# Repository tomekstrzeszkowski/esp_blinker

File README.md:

# Motivation

In recent years, there has been a significant rise in the usage of digital devices across all age brackets, whether for work or leisure. Various therapeutic and management approaches have been suggested to address this issue, encompassing optical, medical, and ergonomic interventions.

One common recommendation from clinicians is to take regular breaks to reduce digital eye strain. This advice often includes following the 20-20-20 rule, which suggests taking breaks to focus on an object at least 20 feet (6 meters) away for at least 20 seconds every 20 minutes.

This project serves as a reminder to perform these exercises by toggling your external device on and off, ideally accompanied by a light indicator.

# Hardware 

## Electrical components and flashing

Full details are available in pcb folder
 - ESP8266 (ESP-12F)
 - Relay
 - SMD resistors
 - Button switches
 - Power supply

[PCB & Flashing](pcb/README.md)
 
# MQTT

## Home assistant

In devices & services add integration and search for MQTT. Add default integration.
In Apps, install app `Mosquitto broker`. Then go to config and add entry to logins.
Add new entry under MQTT and configure device, use `esp32/gpio/set` and switch component.

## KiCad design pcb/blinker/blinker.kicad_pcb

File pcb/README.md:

# PIN out

## 4 Socket PINs (J1)

1 - GND
2 - 3V3
3 - GPIO 3 / RXD
4 - GPIO 1 / TXD

## 2 Socket PINs

1, 2 GPIO0 - Boot up PINS (J2), connect for entering flashing mode

# Wiring ConnectionsUSB-to-UART 

 - USB TX - Connect to GPIO3 (RXD) on the ESP 
 - USB RX - Connect to GPIO1 (TXD) on the ESP
 - GND - Connect adapter GND to ESP GND

Enter into flashing mode
 - GPIO0 - Connect to GND, just connect 1 with 2 togeter via jumper

# Flashing
 - Connect UART to USB converter to J1, don't connect to USB yet
 - Enter flashing mode, connect 2 PINs together using jumper in J2 socket
 - Connect converter to USB, The blue LED should flicker once
 - Follow your preferred flashing IDE

## VS Code and PlatformIO

 - On the bottom bar, select esp12e, ttyUSB0
 - Click PlatformIO upload

At this point you should see percentage progress and LED should flash in some intervals

## esptool and PlatformIO

 - Install requirements.txt, this should install esptool and PlatformIO
 - PlatformIO builds firmware in this location
```
blinker/.pio/build/esp12e/firmware.bin
```
 - Build `firmware.bin` (list available targets `pio run --list-targets`)

```
pio run -e esp12e
```
This should produce firmware in the location as above.

 - Flash
```
esptool --port /dev/ttyUSB0 write-flash 0x00000 blinker/.pio/build/esp12e/firmware.bin
```

For ESP32

```
esptool --port /dev/ttyUSB0 --chip esp32 write-flash 0x10000 firmware.bin
```

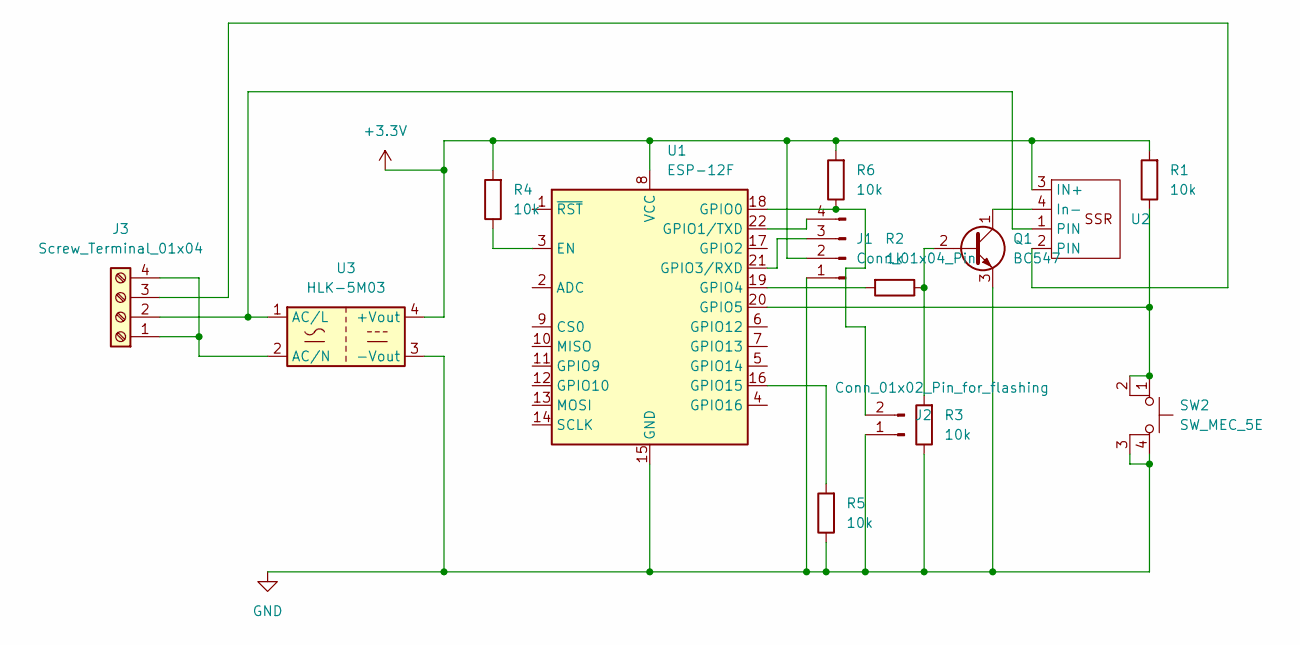
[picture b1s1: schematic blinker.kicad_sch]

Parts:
J1: Conn_01x04_Pin; PinHeader_1x04_P2.00mm_Vertical
J2: Conn_01x02_Pin_for_flashing; PinHeader_1x02_P2.00mm_Vertical
J3: Screw_Terminal_01x04; TerminalBlock_MaiXu_MX126-5.0-04P_1x04_P5.00mm
Q1: BC547; TO-92_Inline
R1, R3, R4, R5, R6: 10k; R_0805_2012Metric_Pad1.20x1.40mm_HandSolder
R2: 1k; R_0805_2012Metric_Pad1.20x1.40mm_HandSolder
SW2: SW_MEC_5E; SW_MEC_5GSH9
U1: ESP-12F; ESP-12E
U2: SSR-D3803HK
U3: HLK-5M03; Converter_ACDC_Hi-Link_HLK-5Mxx

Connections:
+3.3V: J1.2, R1.2, R4.2, R6.2, U1.8 (VCC), U2.3 (IN+), U3.4 (+Vout)
GND: J1.1, J2.1, Q1.3 (E), R3.1, R5.1, SW2.3 (K), SW2.4 (A), U1.15 (GND), U3.3 (-Vout)
unnamed: J1.3, U1.21 (GPIO3/RXD)
unnamed: J1.4, U1.22 (GPIO1/TXD)
unnamed: J2.2, R6.1, U1.18 (GPIO0)
unnamed: J3.1, J3.4, U3.2 (AC/N)
unnamed: J3.2, U2.1 (PIN), U3.1 (AC/L)
unnamed: J3.3, U2.2 (PIN)
unnamed: Q1.2 (B), R2.1, R3.2
unnamed: Q1.1 (C), U2.4 (In-)
unnamed: R4.1, U1.3 (EN)
unnamed: R2.2, U1.19 (GPIO4)
unnamed: R1.1, SW2.1, SW2.2, U1.20 (GPIO5)
unnamed: R5.2, U1.16 (GPIO15)

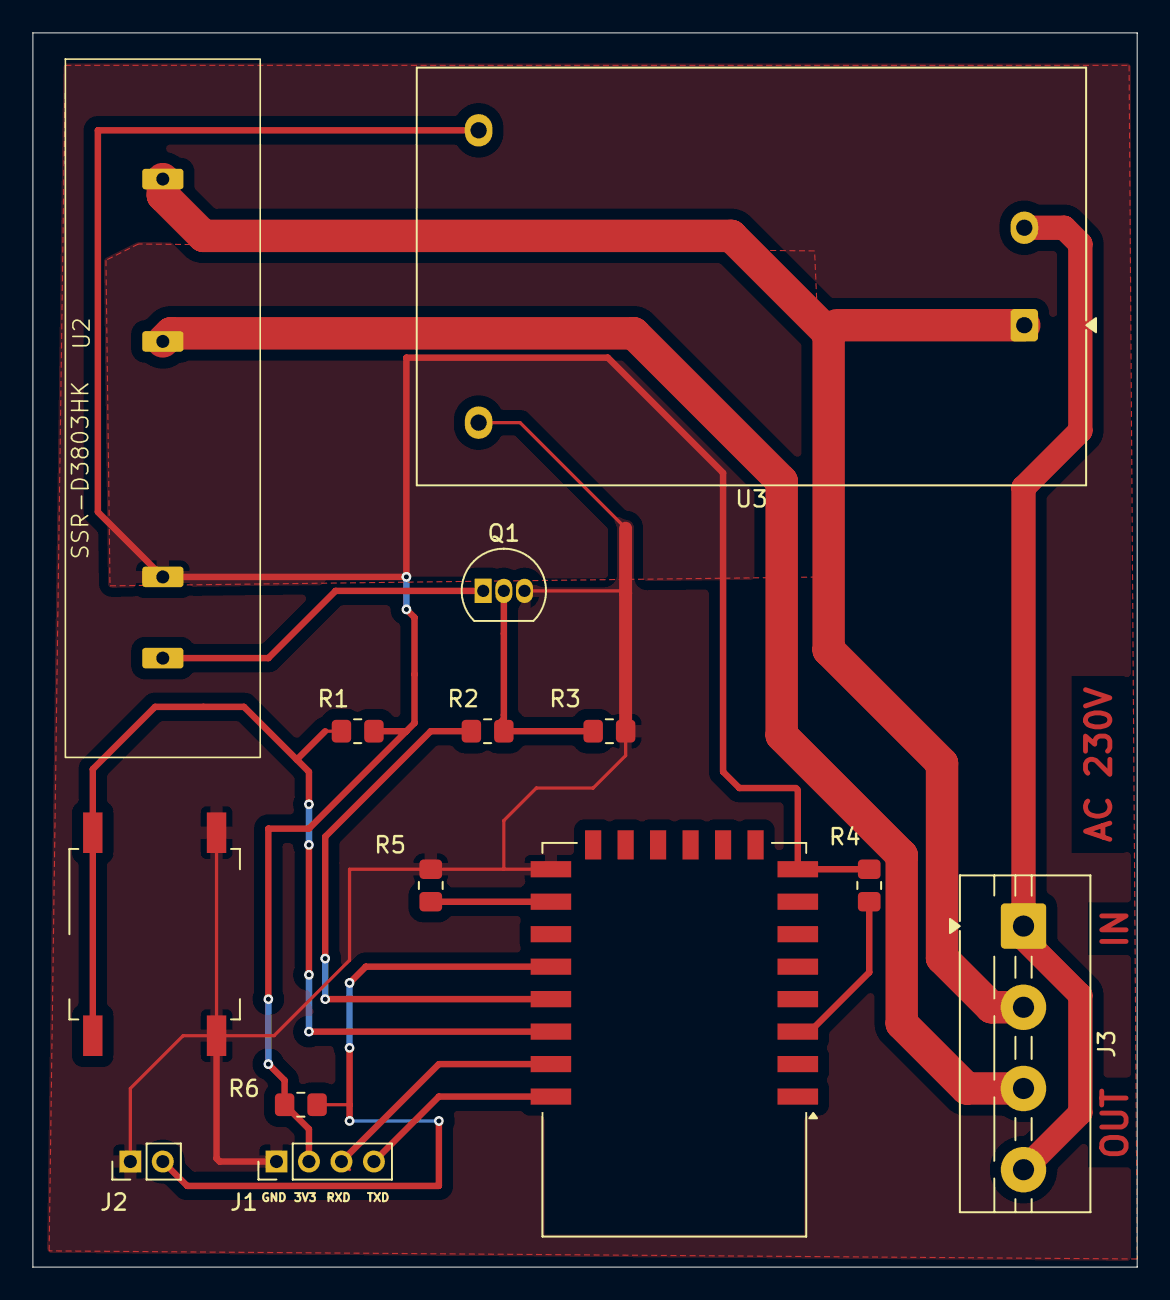
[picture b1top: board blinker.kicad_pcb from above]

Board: 2 copper layers, 68.0 x 76.0 mm, 14 parts (0 on the bottom side), 14 nets.

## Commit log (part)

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2026-06-06 Add blinker
2026-06-06 Add ignore files
2026-06-06 Add motivation section to README.md
    Added motivation section explaining the purpose of the project and its relevance to digital eye strain management.
2026-06-06 Move libraries to lib
2026-06-06 Add button
2026-06-07 Add MQTT connectivity
2026-06-07 Publish correct state to MQTT
2026-06-07 Clean up code
2026-06-07 Remove manual override
2026-06-07 Prevent from unnecessary digital writes
2026-06-08 Unlock setup when wifi is not available
2026-06-10 Add ESP8266
2026-06-14 Use wrapper instead of lambda function for ESP8266 compatibility
2026-06-14 Generic gpio channel
2026-06-14 Add some doc
2026-06-15 Generic MQTT props names, WDT feed preventing resets, Generic config
2026-06-22 Add ESP32dev, Add home assistant ESPHome builder script
2026-06-22 Add on time sync for daylight detection
2026-06-22 Update doc for generic
2026-06-29 Add PCB
